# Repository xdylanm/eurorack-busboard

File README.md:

# eurorack-busboard
Simple passive bus board for power distribution

There are many good examples of these out there already, e.g. (David Haillant's)[http://www.davidhaillant.com/category/electronic-projects/eurorack-power-bus/compact-16-pin-eurorack-power-bus-board/]. Probably better to just use those, but this project will also be an effort to create a CI/CD process for hardware captured in KiCAD.

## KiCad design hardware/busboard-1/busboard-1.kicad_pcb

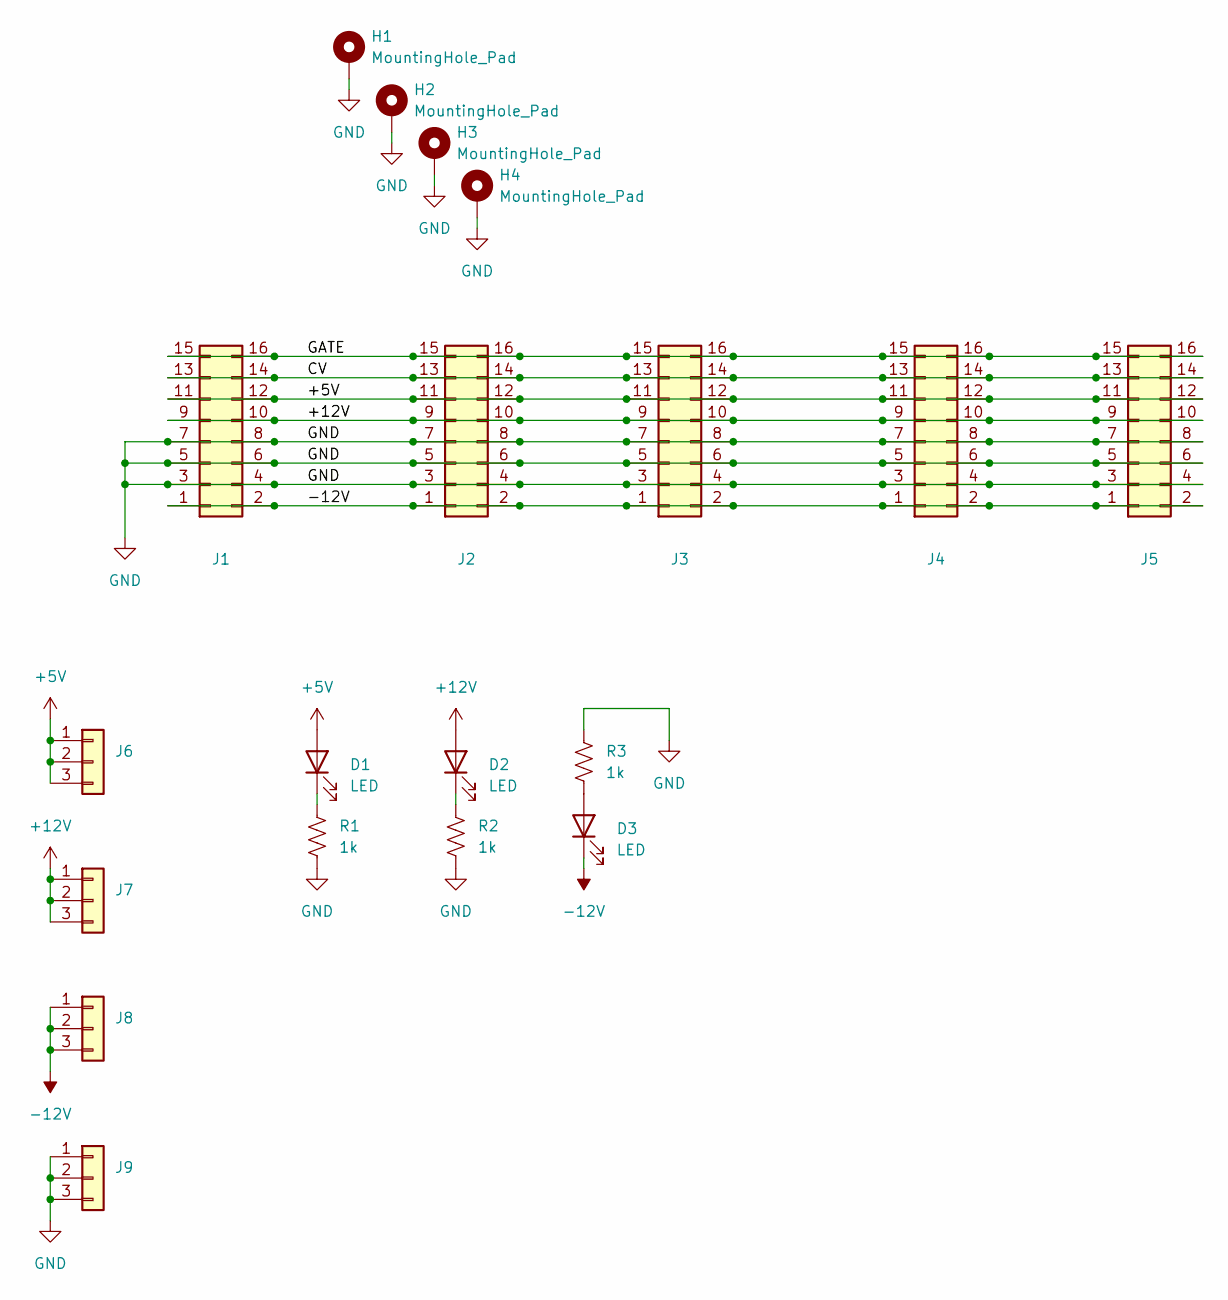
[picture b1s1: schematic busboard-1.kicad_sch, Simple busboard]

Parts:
D1, D2, D3: LED; LED_D5.0mm
H1, H2, H3, H4: MountingHole_Pad; MountingHole_4.3mm_M4_ISO14580_Pad
J1, J2, J3, J4, J5: Conn_02x08_Odd_Even; IDC-Header_2x08_P2.54mm_Vertical
J6, J7, J8, J9: Conn_01x03; PinHeader_1x03_P2.54mm_Vertical
R1, R2, R3: 1k; R_Axial_DIN0207_L6.3mm_D2.5mm_P2.54mm_Vertical

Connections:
+5V: D1.2 (A), J1.11, J1.12, J2.11, J2.12, J3.11, J3.12, J4.11, J4.12, J5.11, J5.12, J6.1, J6.2, J6.3
+12V: D2.2 (A), J1.9, J1.10, J2.9, J2.10, J3.9, J3.10, J4.9, J4.10, J5.9, J5.10, J7.1, J7.2, J7.3
-12V: D3.1 (K), J1.1, J1.2, J2.1, J2.2, J3.1, J3.2, J4.1, J4.2, J5.1, J5.2, J8.1, J8.2, J8.3
/CV: J1.13, J1.14, J2.13, J2.14, J3.13, J3.14, J4.13, J4.14, J5.13, J5.14
/GATE: J1.15, J1.16, J2.15, J2.16, J3.15, J3.16, J4.15, J4.16, J5.15, J5.16
GND: H1.1, H2.1, H3.1, H4.1, J1.3, J1.4, J1.5, J1.6, J1.7, J1.8, J2.3, J2.4, J2.5, J2.6, J2.7, J2.8, J3.3, J3.4, J3.5, J3.6, J3.7, J3.8, J4.3, J4.4, J4.5, J4.6, J4.7, J4.8, J5.3, J5.4, J5.5, J5.6, J5.7, J5.8, J9.1, J9.2, J9.3, R1.2, R2.2, R3.1
unnamed: D1.1 (K), R1.1
unnamed: D2.1 (K), R2.1
unnamed: D3.2 (A), R3.2

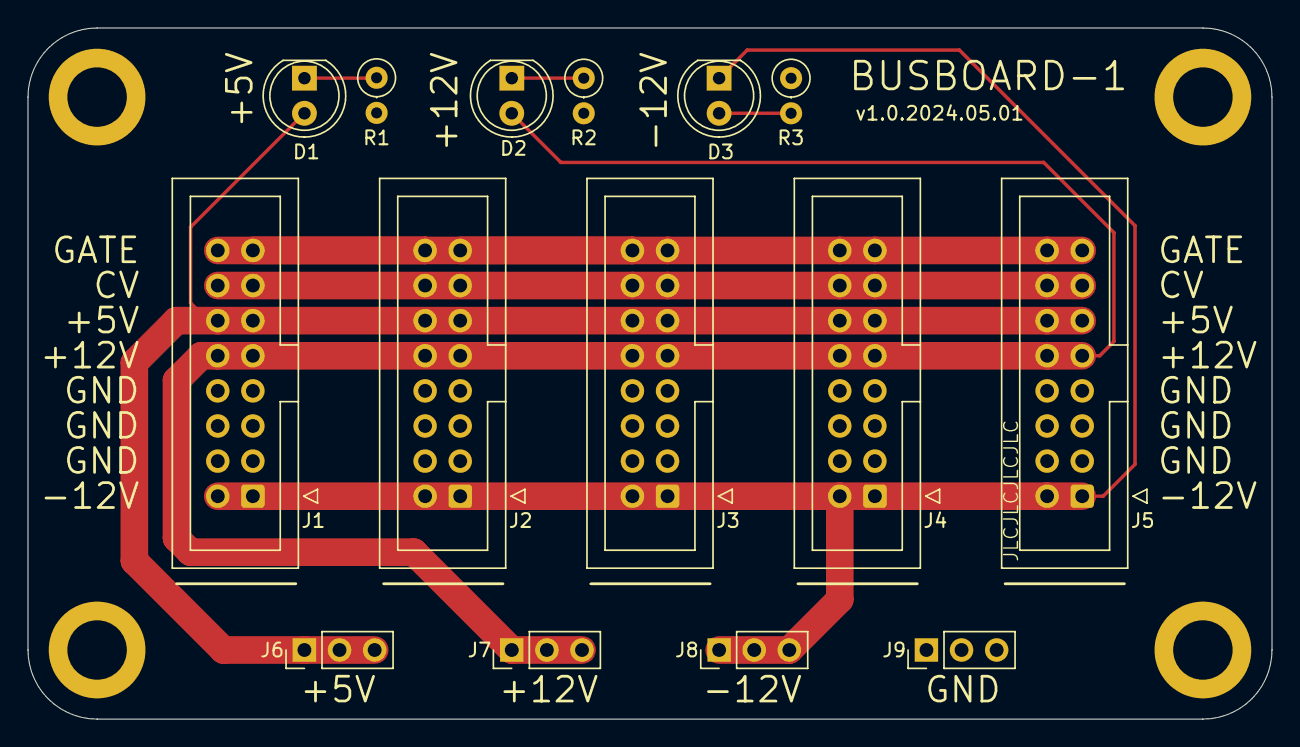
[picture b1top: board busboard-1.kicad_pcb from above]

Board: 2 copper layers, 90.0 x 50.0 mm, 19 parts (0 on the bottom side), 9 nets.

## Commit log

2024-05-02 initial layout and gerbers
2024-05-02 updated README, added PDF of schematic
